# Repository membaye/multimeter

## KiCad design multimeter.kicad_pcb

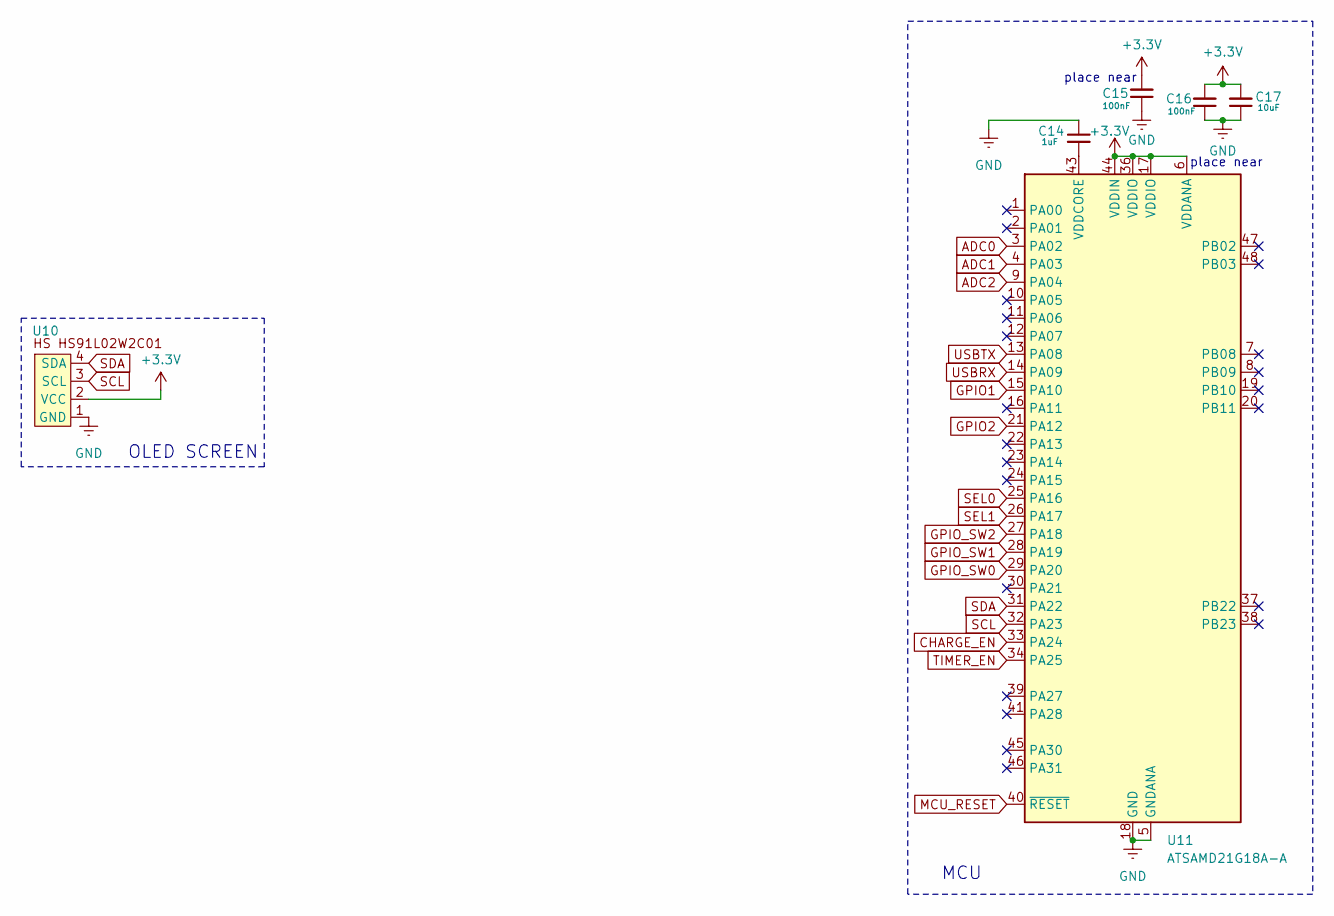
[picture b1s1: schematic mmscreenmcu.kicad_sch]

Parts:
C14: 1uF; C_0402_1005Metric; LCSC# C14445
C15, C16: 100nF; C_0402_1005Metric; LCSC# C22435935
C17: 10uF; C_0603_1608Metric; LCSC# C19702
U10: HS HS91L02W2C01_OLED; LCSC# C5248081
U11: ATSAMD21G18A-A; TQFP-48_7x7mm_P0.5mm; LCSC# C78624

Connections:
+3.3V: C15.2, C16.2, C17.2, U10.2 (VCC), U11.6 (VDDANA), U11.17 (VDDIO), U11.36 (VDDIO), U11.44 (VDDIN); also elsewhere on the board
ADC0: U11.3 (PA02); also elsewhere on the board
ADC1: U11.4 (PA03); also elsewhere on the board
ADC2: U11.9 (PA04); also elsewhere on the board
CHARGE_EN: U11.33 (PA24); also elsewhere on the board
GND: C14.1, C15.1, C16.1, C17.1, U10.1 (GND), U11.5 (GNDANA), U11.18 (GND), U11.35 (GND), U11.42 (GND); also elsewhere on the board
GPIO1: U11.15 (PA10); also elsewhere on the board
GPIO2: U11.21 (PA12); also elsewhere on the board
GPIO_SW0: U11.29 (PA20); also elsewhere on the board
GPIO_SW1: U11.28 (PA19); also elsewhere on the board
GPIO_SW2: U11.27 (PA18); also elsewhere on the board
MCU_RESET: U11.40 (~RESET); also elsewhere on the board
unnamed: C14.2, U11.43 (VDDCORE)
SCL: U10.3 (SCL), U11.32 (PA23)
SDA: U10.4 (SDA), U11.31 (PA22)
SEL0: U11.25 (PA16); also elsewhere on the board
SEL1: U11.26 (PA17); also elsewhere on the board
TIMER_EN: U11.34 (PA25); also elsewhere on the board
USBRX: U11.14 (PA09); also elsewhere on the board
USBTX: U11.13 (PA08); also elsewhere on the board

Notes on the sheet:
place near
OLED SCREEN
MCU

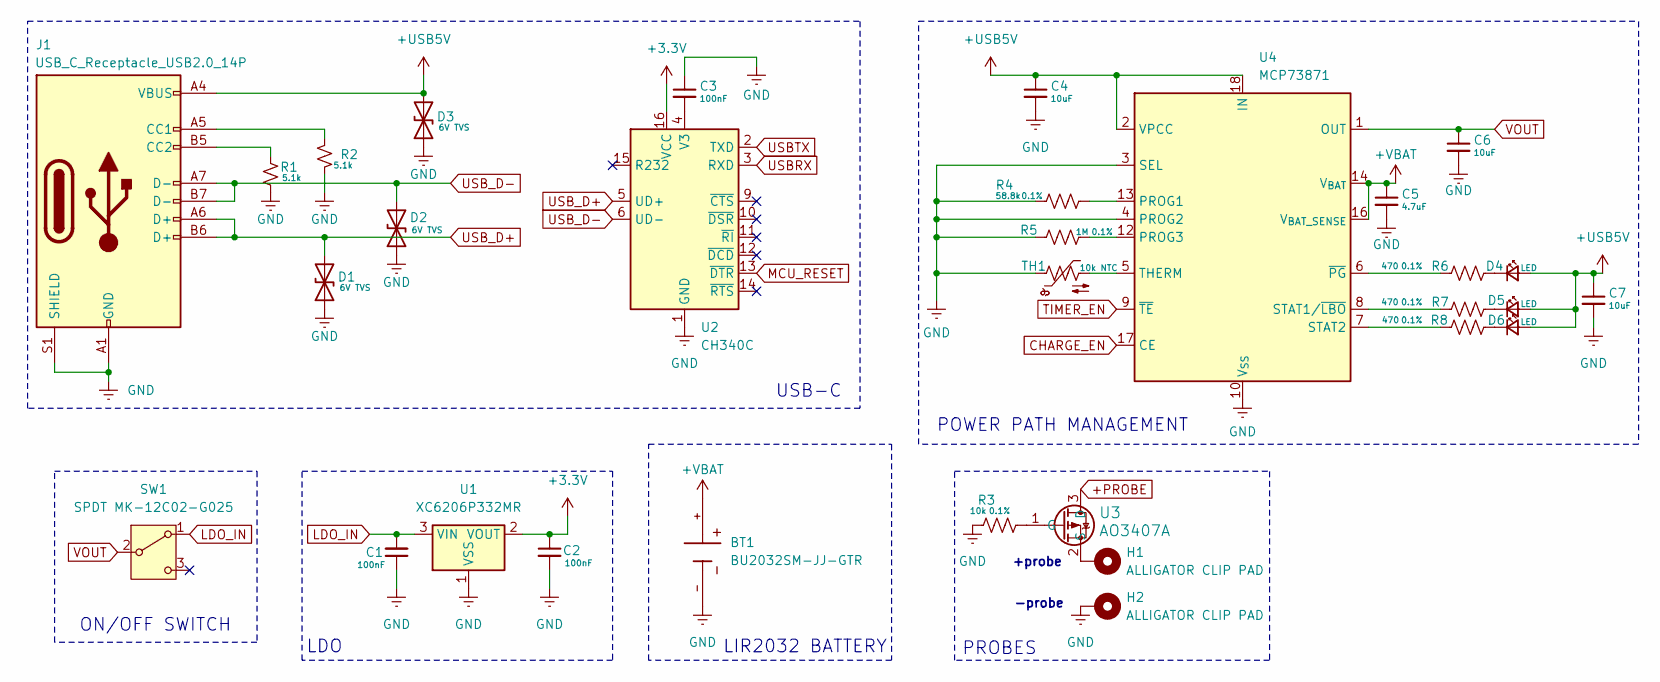
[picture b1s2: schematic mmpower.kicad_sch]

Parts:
BT1: BU2032SM-JJ-GTR; BAT_BU2032SM-JJ-GTR; PARTREV H; LCSC# C7091834
C1, C2, C3: 100nF; C_0402_1005Metric; LCSC# C22435935
C4, C6, C7: 10uF; C_0603_1608Metric; LCSC# C19702
C5: 4.7uF; C_0402_1005Metric; LCSC# C368809
D1, D2, D3: 6V TVS; D_0402_1005Metric; LCSC# C316043
D4, D5, D6: LED; LED_0402_1005Metric; LCSC# C364550
H1, H2: ALLIGATOR CLIP PAD; TestPoint_THTPad_4.0x4.0mm_Drill2.0mm
J1: USB_C_Receptacle_USB2.0_14P; USB_C_Receptacle_GCT_USB4105-xx-A_16P_TopMnt_Horizontal; MPN C165948; LCSC# C165948
R1, R2: 5.1k; R_0402_1005Metric; LCSC# C490833
R3: 10k; R_0402_1005Metric; Tolerance 0.1%; LCSC# C490830
R4: 58.8k; R_0402_1005Metric; Tolerance 0.1%; LCSC# C2692947
R5: 1M; R_0402_1005Metric; Tolerance 0.1%; LCSC# C4334825
R6, R7, R8: 470; R_0402_1005Metric; Tolerance 0.1%; LCSC# C445590
SW1: SPDT MK-12C02-G025; MK-12C02_SW; LCSC# C778186
TH1: 10k NTC; R_0402_1005Metric; LCSC# C3154163
U1: XC6206P332MR; SOT-23; LCSC# C347376
U2: CH340C; SOIC-16_3.9x9.9mm_P1.27mm; LCSC# C84681
U3: AO3407A; SOT-23-3L_AOS; LCSC# C7436553
U4: MCP73871; QFN-20-1EP_4x4mm_P0.5mm_EP2.5x2.5mm; LCSC# C511310

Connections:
+3.3V: C2.1, U1.2 (VOUT), U2.16 (VCC); also elsewhere on the board
+PROBE: U3.3 (D); also elsewhere on the board
+USB5V: C4.1, C7.1, D3.2 (A2), D4.2 (A), D5.2 (A), D6.2 (A), J1.A4 (VBUS), J1.A9 (VBUS), J1.B4 (VBUS), J1.B9 (VBUS), U4.2 (VPCC), U4.18 (IN), U4.19 (IN)
+VBAT: BT1.+, C5.1, U4.14 (V_{BAT}), U4.15 (V_{BAT}), U4.16 (V_{BAT_SENSE}); also elsewhere on the board
CHARGE_EN: U4.17 (CE); also elsewhere on the board
GND: BT1.-, C1.1, C2.2, C3.1, C4.2, C5.2, C6.2, C7.2, D1.1 (A1), D2.1 (A1), D3.1 (A1), H2.1, J1.A1 (GND), J1.A12 (GND), J1.B1 (GND), J1.B12 (GND), J1.S1 (SHIELD), R1.2, R2.2, R3.1, R4.1, R5.2, TH1.1, U1.1 (VSS), U2.1 (GND), U4.3 (SEL), U4.4 (PROG2), U4.10 (V_{SS}), U4.11 (V_{SS}), U4.21 (V_{SS}); also elsewhere on the board
LDO_IN: C1.2, SW1.1 (A), U1.3 (VIN)
MCU_RESET: U2.13 (~DTR); also elsewhere on the board
unnamed: D4.1 (K), R6.2
unnamed: D5.1 (K), R7.2
unnamed: D6.1 (K), R8.1
unnamed: J1.A5 (CC1), R2.1
unnamed: J1.B5 (CC2), R1.1
unnamed: C3.2, U2.4 (V3)
unnamed: R3.2, U3.1 (G)
unnamed: H1.1, U3.2 (S)
unnamed: R4.2, U4.13 (PROG1)
unnamed: R5.1, U4.12 (PROG3)
unnamed: R7.1, U4.8 (STAT1/~LBO)
unnamed: R8.2, U4.7 (STAT2)
unnamed: TH1.2, U4.5 (THERM)
unnamed: R6.1, U4.6 (~PG)
TIMER_EN: U4.9 (~TE); also elsewhere on the board
USBRX: U2.3 (RXD); also elsewhere on the board
USBTX: U2.2 (TXD); also elsewhere on the board
USB_D+: D1.2 (A2), J1.A6 (D+), J1.B6 (D+), U2.5 (UD+)
USB_D-: D2.2 (A2), J1.A7 (D-), J1.B7 (D-), U2.6 (UD-)
VOUT: C6.1, SW1.2 (B), U4.1 (OUT), U4.20 (OUT)

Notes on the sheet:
POWER PATH MANAGEMENT
LIR2032 BATTERY
+probe
ON/OFF SWITCH
-probe
LDO
PROBES
USB-C

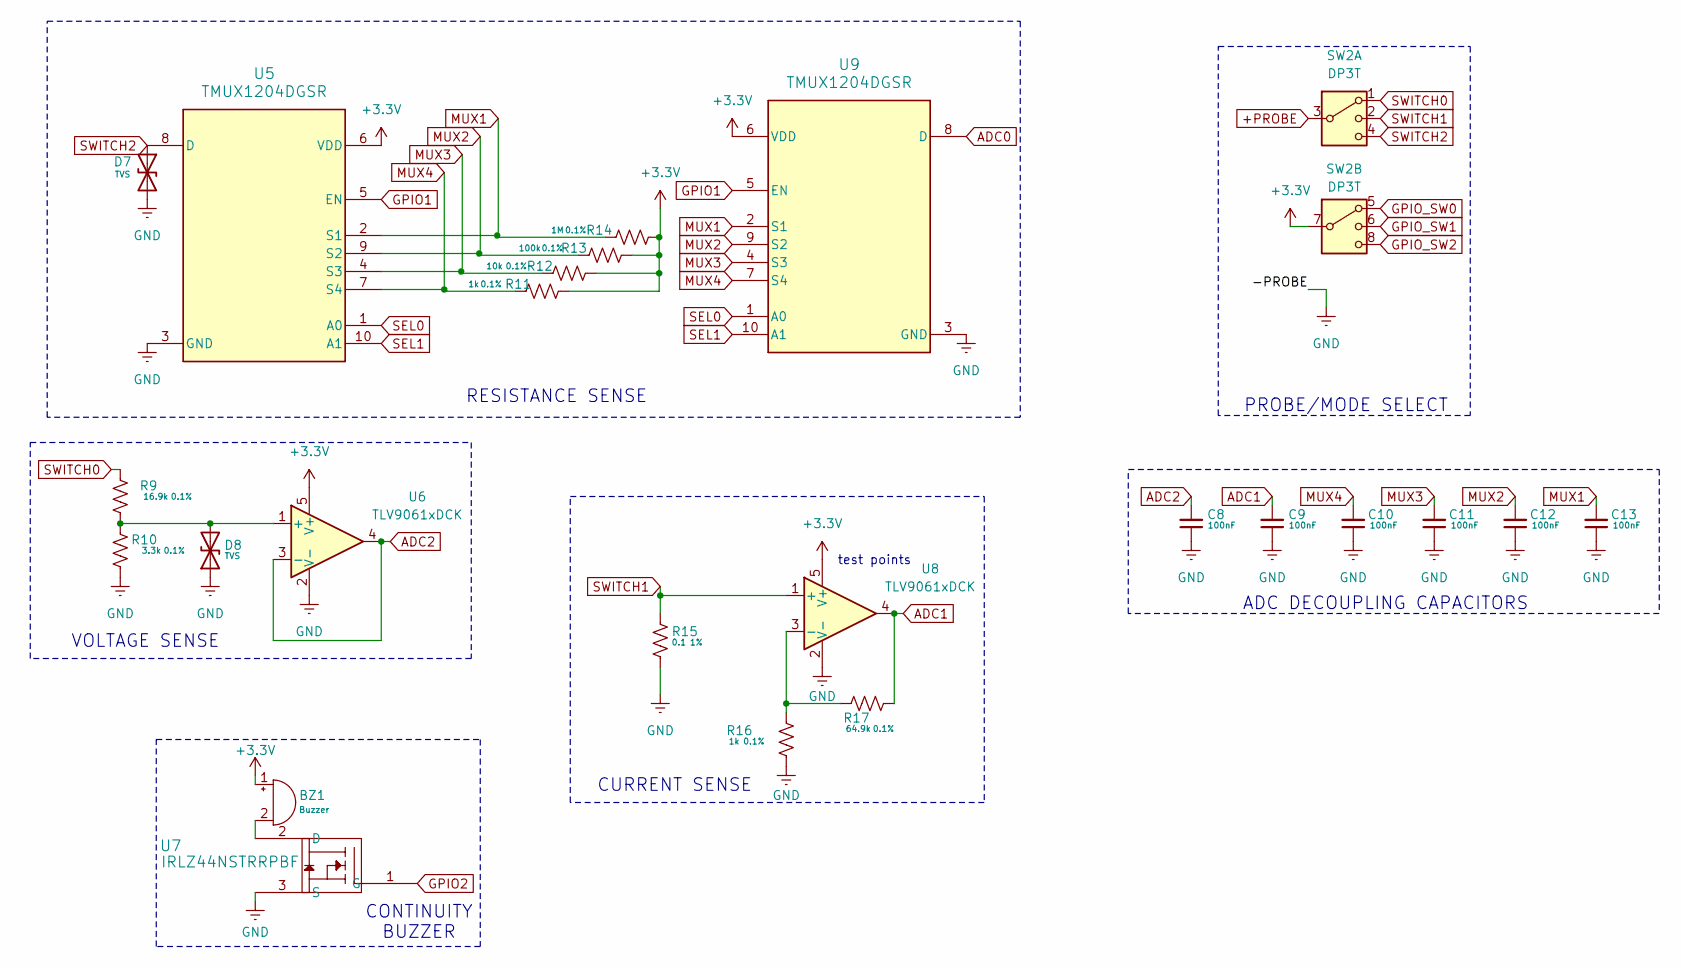
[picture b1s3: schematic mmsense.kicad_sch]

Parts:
BZ1: Buzzer; SM_CPT_9X9_CUD; LCSC# C95163
C8, C9, C10, C11, C12, C13: 100nF; C_0402_1005Metric; LCSC# C22435935
D7, D8: TVS; D_0402_1005Metric; LCSC# C1973257
R9: 16.9k; R_0402_1005Metric; Tolerance 0.1%; LCSC# C852563
R10: 3.3k; R_0402_1005Metric; Tolerance 0.1%; LCSC# C445607
R11, R16: 1k; R_0402_1005Metric; Tolerance 0.1%; LCSC# C445596
R12: 10k; R_0402_1005Metric; Tolerance 0.1%; LCSC# C490830
R13: 100k; R_0402_1005Metric; Tolerance 0.1%; LCSC# C445619
R14: 1M; R_0402_1005Metric; Tolerance 0.1%; LCSC# C4334825
R15: 0.1; R_0402_1005Metric; Tolerance 1%; LCSC# C4122454
R17: 64.9k; R_0402_1005Metric; Tolerance 0.1%; LCSC# C490835
SW2: DP3T; SW-TH_SK-23D05-G070; LCSC# C2848890
U5, U9: TMUX1204DGSR; DGS0010A-MFG; LCSC# C2840022
U6, U8: TLV9061xDCK; SOT-353_SC-70-5; LCSC# C398357
U7: IRLZ44NSTRRPBF; TRANS_IRLZ44NSTRL_INF; LCSC# C2680878

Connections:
+3.3V: BZ1.1 (+), R11.1, R12.1, R13.1, R14.1, SW2.7, U5.6 (VDD), U6.5 (V+), U8.5 (V+), U9.6 (VDD); also elsewhere on the board
+PROBE: SW2.3; also elsewhere on the board
ADC0: U9.8 (D); also elsewhere on the board
ADC1: C9.2, R17.2, U8.4; also elsewhere on the board
ADC2: C8.2, U6.3 (-), U6.4; also elsewhere on the board
GND: C8.1, C9.1, C10.1, C11.1, C12.1, C13.1, D7.2 (A2), D8.1 (A1), R10.1, R15.2, R16.2, U5.3 (GND), U6.2 (V-), U7.3 (S), U8.2 (V-), U9.3 (GND); also elsewhere on the board
GPIO1: U5.5 (EN), U9.5 (EN); also elsewhere on the board
GPIO2: U7.1 (G); also elsewhere on the board
GPIO_SW0: SW2.5; also elsewhere on the board
GPIO_SW1: SW2.6; also elsewhere on the board
GPIO_SW2: SW2.8; also elsewhere on the board
MUX1: C13.2, R14.2, U5.2 (S1), U9.2 (S1)
MUX2: C12.2, R13.2, U5.9 (S2), U9.9 (S2)
MUX3: C11.2, R12.2, U5.4 (S3), U9.4 (S3)
MUX4: C10.2, R11.2, U5.7 (S4), U9.7 (S4)
unnamed: BZ1.2 (-), U7.2 (D)
unnamed: D8.2 (A2), R9.1, R10.2, U6.1 (+)
unnamed: R16.1, R17.1, U8.3 (-)
SEL0: U5.1 (A0), U9.1 (A0); also elsewhere on the board
SEL1: U5.10 (A1), U9.10 (A1); also elsewhere on the board
SWITCH0: R9.2, SW2.1
SWITCH1: R15.1, SW2.2, U8.1 (+)
SWITCH2: D7.1 (A1), SW2.4, U5.8 (D)

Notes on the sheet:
ADC DECOUPLING CAPACITORS
RESISTANCE SENSE
test points
CONTINUITY BUZZER
PROBE/MODE SELECT
CURRENT SENSE
VOLTAGE SENSE

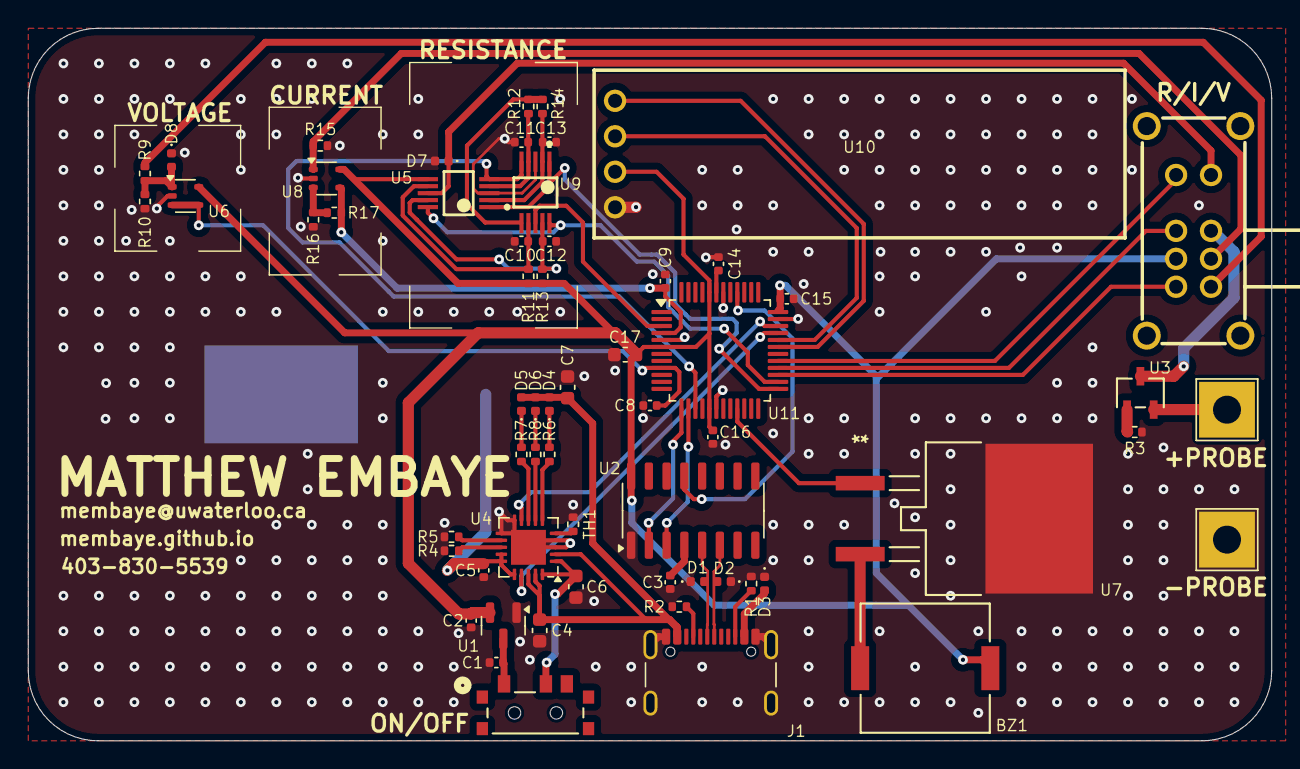
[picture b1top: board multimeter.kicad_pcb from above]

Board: 2 copper layers, 89.0 x 51.0 mm, 61 parts (1 on the bottom side), 51 nets.

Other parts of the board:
BATTERY: BU2032SM-JJ-GTR; BAT_BU2032SM-JJ-GTR

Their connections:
+VBAT: BATTERY.+; also elsewhere on the board
GND: BATTERY.-; also elsewhere on the board

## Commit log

2025-03-04 Updated Grid
